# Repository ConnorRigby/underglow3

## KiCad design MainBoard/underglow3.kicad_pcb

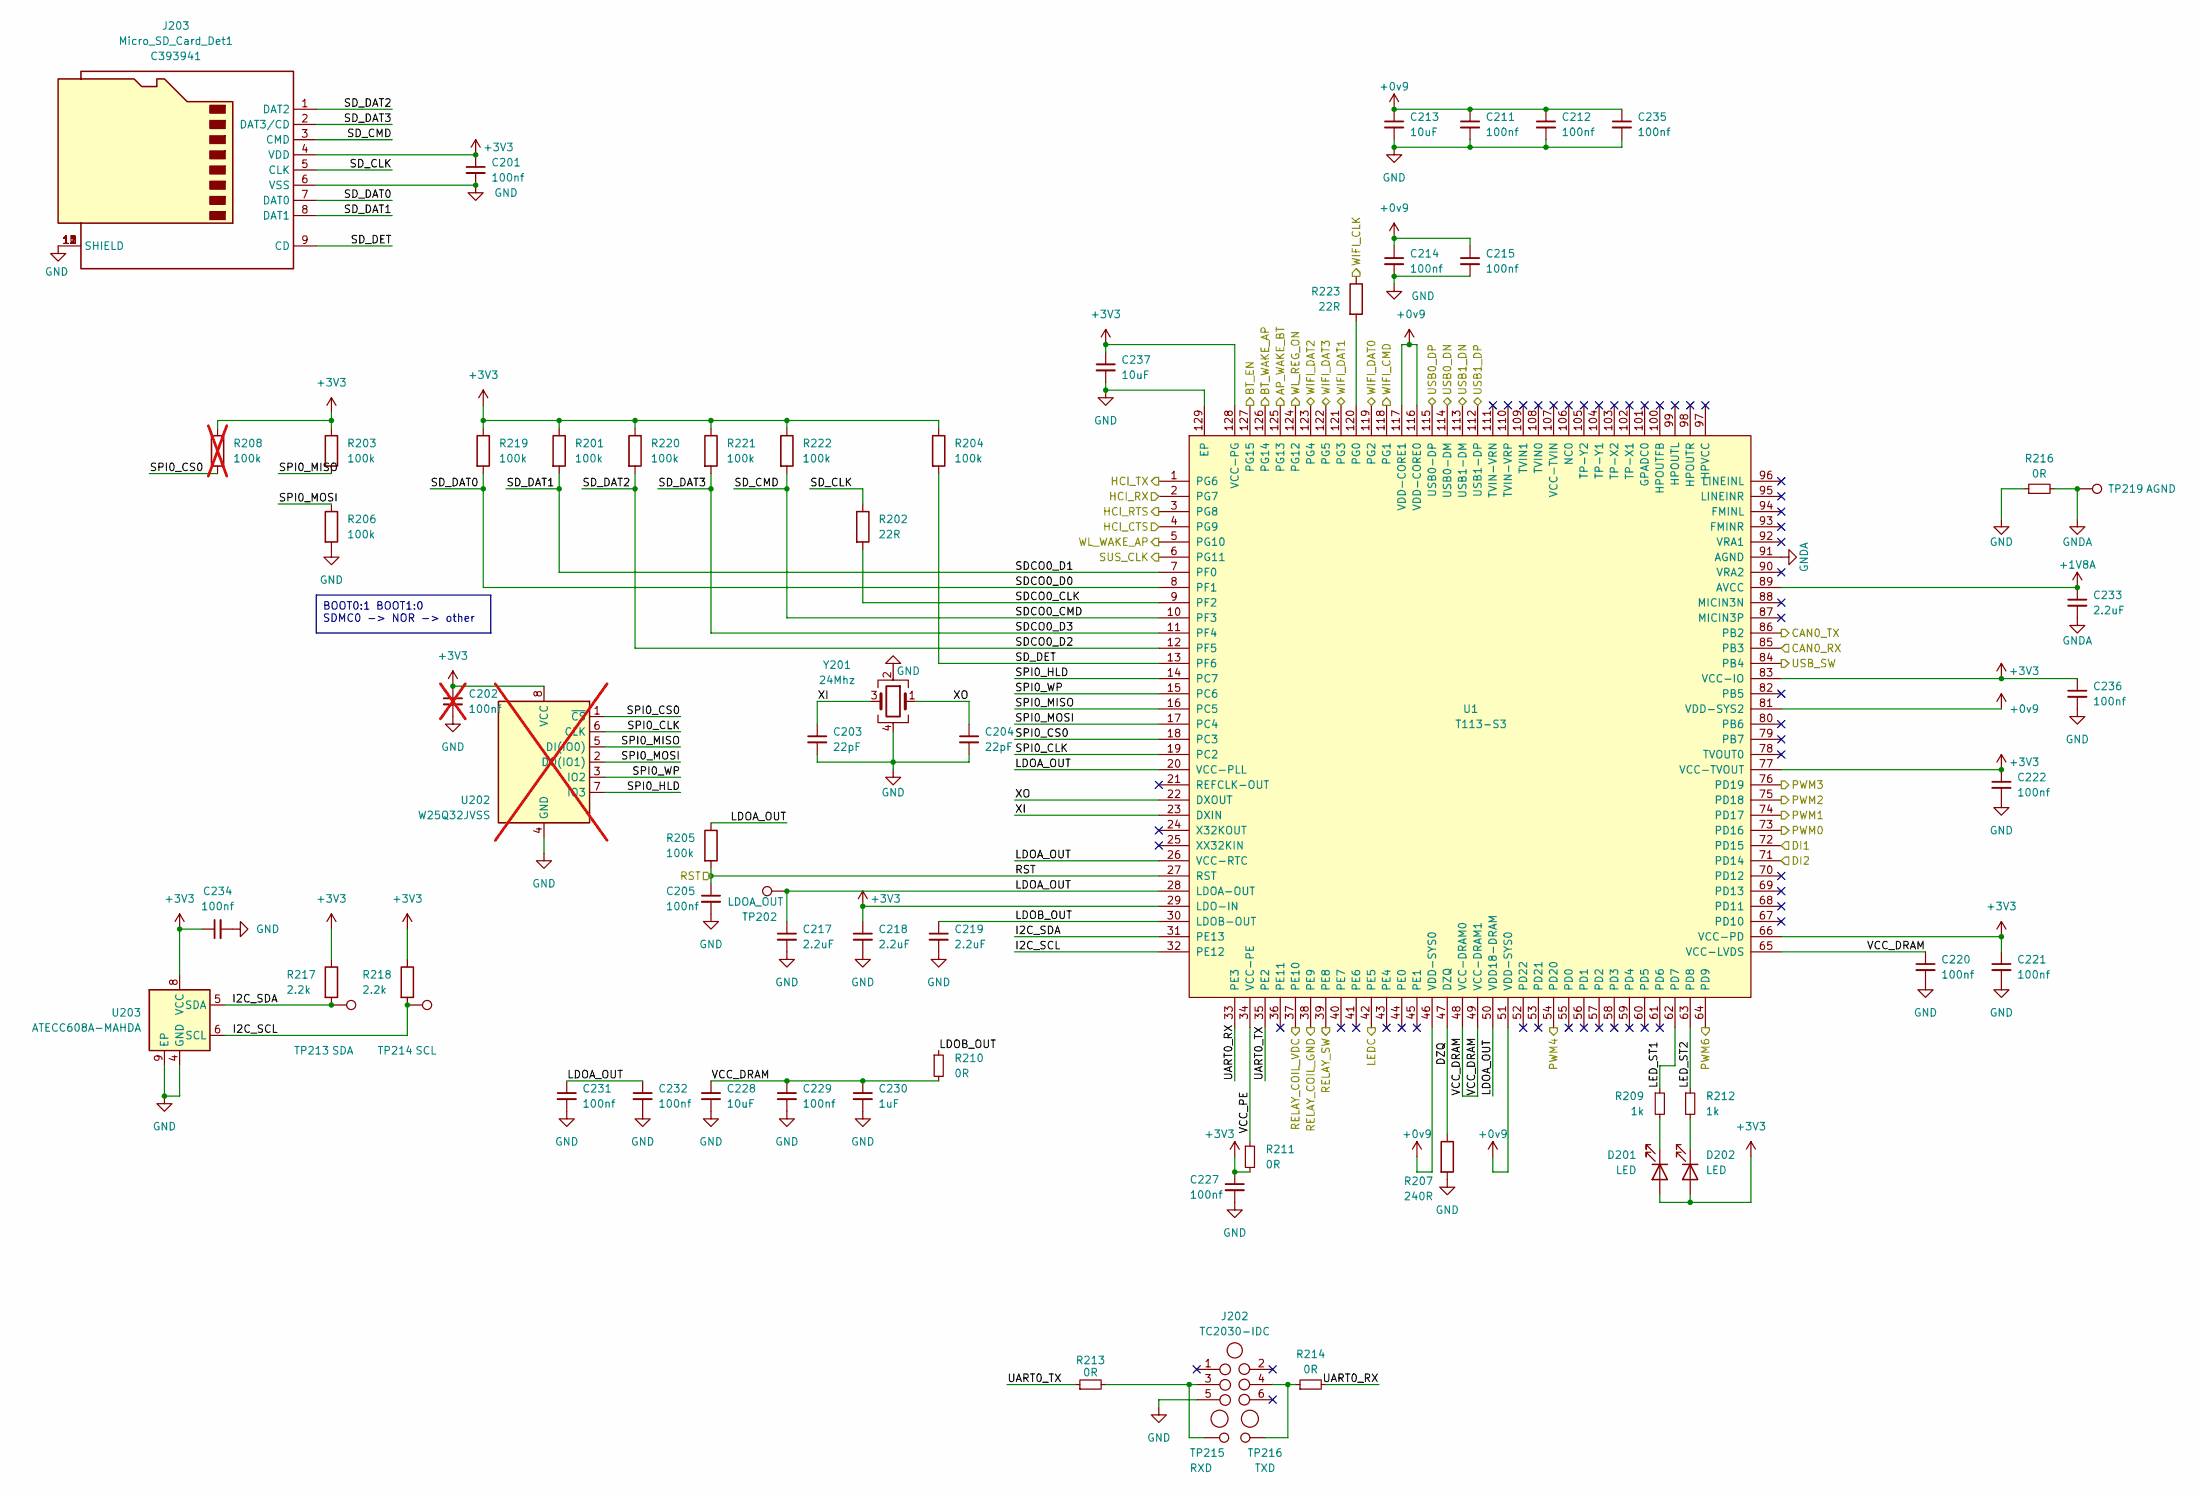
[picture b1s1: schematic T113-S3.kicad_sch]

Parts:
C201, C205, C211, C212, C214, C215, C220, C221, C222, C227, C229, C231, C232, C234, C235, C236: 100nf; C_0402_1005Metric; MPN CL05B104KB54PNC; LCSC C307331
C202: 100nf; C_0402_1005Metric; MPN CL05B104KB54PNC; LCSC C307331; not fitted
C203, C204: 22pF; C_0402_1005Metric; MPN 0402CG220J500NT; LCSC C1555
C213, C228, C237: 10uF; C_0603_1608Metric; MPN CL10A106MA8NRNC; LCSC C96446
C217, C218, C219, C233: 2.2uF; R_0402_1005Metric; MPN CL05A225MQ5NSNC; LCSC C12530
C230: 1uF; R_0402_1005Metric; MPN CL05A105KA5NQNC; LCSC C52923
D201, D202: LED; LED_0402_1005Metric; MPN LTST-C281KRKT; LCSC C364556
J202: TC2030-IDC; Tag-Connect_TC2030-IDC-NL_2x03_P1.27mm_Vertical; MPN TC2030-IDC
J203: Micro_SD_Card_Det1; TF-SMD_TF-PUSH; MPN TF PUSH; LCSC C393941
R201, R203, R204, R205, R206, R219, R220, R221, R222: 100k; R_0402_1005Metric; MPN 0402WGF1003TCE; LCSC C25741
R202, R223: 22R; R_0402_1005Metric; MPN 0402WGF220JTCE; LCSC C25092
R207: 240R; R_0402_1005Metric; MPN 0402WGF2400TCE; LCSC C25094
R208: 100k; R_0402_1005Metric; MPN 0402WGF1003TCE; LCSC C25741; not fitted
R209, R212: 1k; R_0402_1005Metric; MPN 0402WGF1001TCE; LCSC C11702
R210, R211, R213, R214, R216: 0R; R_0402_1005Metric; MPN 0402WGF0000TCE; LCSC C17168
R217, R218: 2.2k; R_0402_1005Metric; MPN 0402WGF2201TCE; LCSC C25879
TP202: LDOA_OUT; TestPoint_Pad_D1.0mm
TP213: SDA; TestPoint_Pad_D1.0mm
TP214: SCL; TestPoint_Pad_D1.0mm
TP215: RXD; TestPoint_Pad_D1.0mm
TP216: TXD; TestPoint_Pad_D1.0mm
TP219: AGND; TestPoint_Pad_D1.0mm
U1: T113-S3; LQFP-128_L14.0-W14.0-P0.40-LS16.0-BL-EP5.6; MPN T113-S3; LCSC C5197687
U202: W25Q32JVSS; SOIC-8_5.23x5.23mm_P1.27mm; MPN W25Q32JVSSIQ; LCSC C179173; not fitted
U203: ATECC608A-MAHDA; DFN-8-1EP_3x2mm_P0.5mm_EP1.3x1.5mm; MPN ATECC608A-MAHDA-S; LCSC C616908
Y201: 24Mhz; Crystal_SMD_3225-4Pin_3.2x2.5mm; MPN 3TJ424000XYFBC; LCSC C2149059

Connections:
+0v9: C211.1, C212.1, C213.1, C214.1, C215.1, C235.1; also elsewhere on the board
+1V8A: C233.1; also elsewhere on the board
+3V3: C201.1, C202.1, C218.1, C221.1, C222.1, C227.1, C234.1, C236.1, C237.1, D201.2 (A), D202.2 (A), J203.4 (VDD), R201.1, R203.1, R204.1, R208.1, R211.2, R217.1, R218.1, R219.1, R220.1, R221.1, R222.1, U202.8 (VCC), U203.8 (VCC); also elsewhere on the board
/Application/DZQ: R207.1; also elsewhere on the board
/Application/I2C_SCL: R218.2, TP214.1, U203.6 (SCL); also elsewhere on the board
/Application/I2C_SDA: R217.2, TP213.1, U203.5 (SDA); also elsewhere on the board
/Application/LDOA_OUT: C217.1, C231.1, C232.1, R205.1, TP202.1; also elsewhere on the board
/Application/LDOB_OUT: C219.1, R210.1; also elsewhere on the board
/Application/LED_ST1: R209.1; also elsewhere on the board
/Application/LED_ST2: R212.1; also elsewhere on the board
/Application/RST: C205.1, R205.2; also elsewhere on the board
/Application/SDCO0_CLK: R202.2; also elsewhere on the board
/Application/SDCO0_CMD: J203.3 (CMD), R222.2; also elsewhere on the board
/Application/SDCO0_D0: J203.7 (DAT0), R219.2; also elsewhere on the board
/Application/SDCO0_D1: J203.8 (DAT1), R201.2; also elsewhere on the board
/Application/SDCO0_D2: J203.1 (DAT2), R220.2; also elsewhere on the board
/Application/SDCO0_D3: J203.2 (DAT3/CD), R221.2; also elsewhere on the board
/Application/SD_CLK: J203.5 (CLK), R202.1
/Application/SD_DET: J203.9 (CD), R204.2; also elsewhere on the board
/Application/SPI0_CLK: U202.6 (CLK); also elsewhere on the board
/Application/SPI0_CS0: R208.2, U202.1 (~CS); also elsewhere on the board
/Application/SPI0_HLD: U202.7 (IO3); also elsewhere on the board
/Application/SPI0_MISO: R203.2, U202.5 (DI(IO0)); also elsewhere on the board
/Application/SPI0_MOSI: R206.1, U202.2 (DO(IO1)); also elsewhere on the board
/Application/SPI0_WP: U202.3 (IO2); also elsewhere on the board
/Application/UART0_RX: R214.2; also elsewhere on the board
/Application/UART0_TX: R213.1; also elsewhere on the board
/Application/VCC_DRAM: C220.1, C228.1, C229.1, C230.1, R210.2; also elsewhere on the board
/Application/VCC_PE: R211.1; also elsewhere on the board
/Application/WIFI_CLK: R223.1; also elsewhere on the board
/Application/XI: C203.1, Y201.3; also elsewhere on the board
/Application/XO: C204.1, Y201.1; also elsewhere on the board
GND: C201.2, C202.2, C203.2, C204.2, C205.2, C211.2, C212.2, C213.2, C214.2, C215.2, C217.2, C218.2, C219.2, C220.2, C221.2, C222.2, C227.2, C228.2, C229.2, C230.2, C231.2, C232.2, C234.2, C235.2, C236.2, C237.2, J202.5, J203.6 (VSS), J203.10 (SHIELD), J203.11 (SHIELD), J203.12 (SHIELD), J203.13 (SHIELD), R206.2, R207.2, R216.1, U202.4 (GND), U203.4 (GND), U203.9 (EP), Y201.2, Y201.4; also elsewhere on the board
GNDA: C233.2, R216.2, TP219.1; also elsewhere on the board
unnamed: D201.1 (K), R209.2
unnamed: D202.1 (K), R212.2
unnamed: J202.3, R213.2, TP215.1
unnamed: J202.4, R214.1, TP216.1
unnamed 130: R223.2; also elsewhere on the board

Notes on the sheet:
BOOT0:1 BOOT1:0 SDMC0 -> NOR -> other

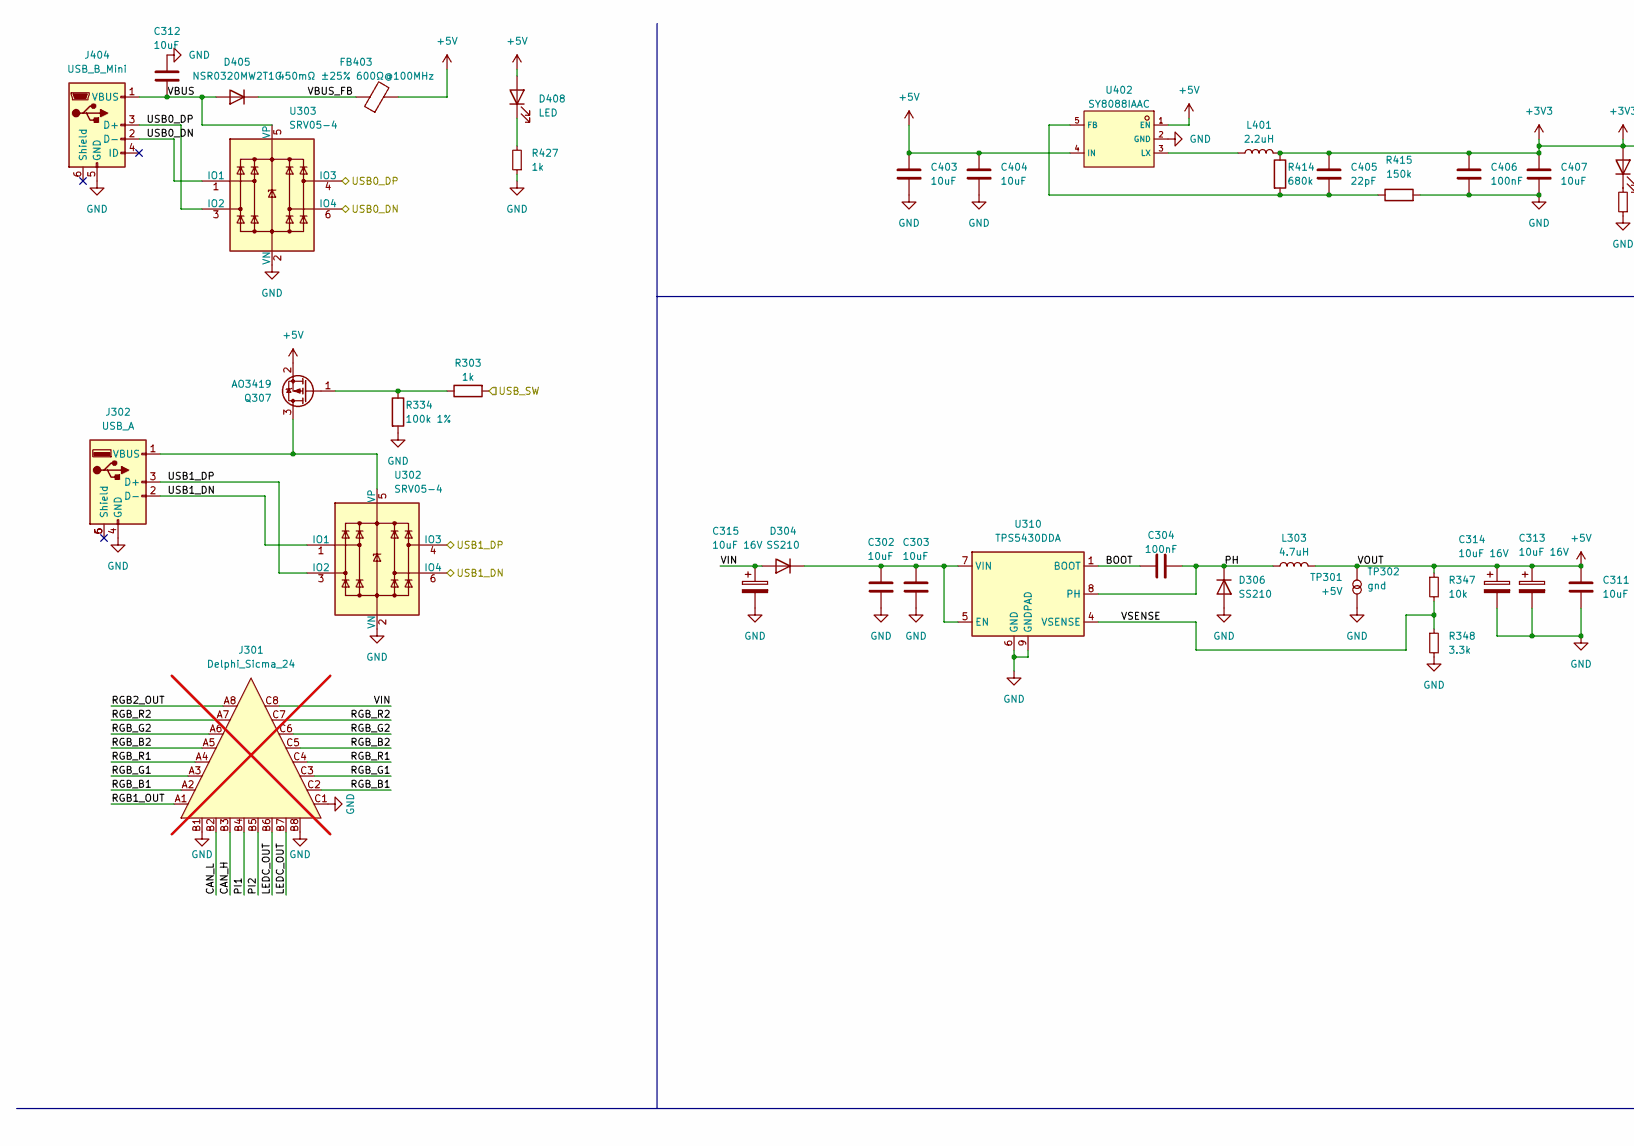
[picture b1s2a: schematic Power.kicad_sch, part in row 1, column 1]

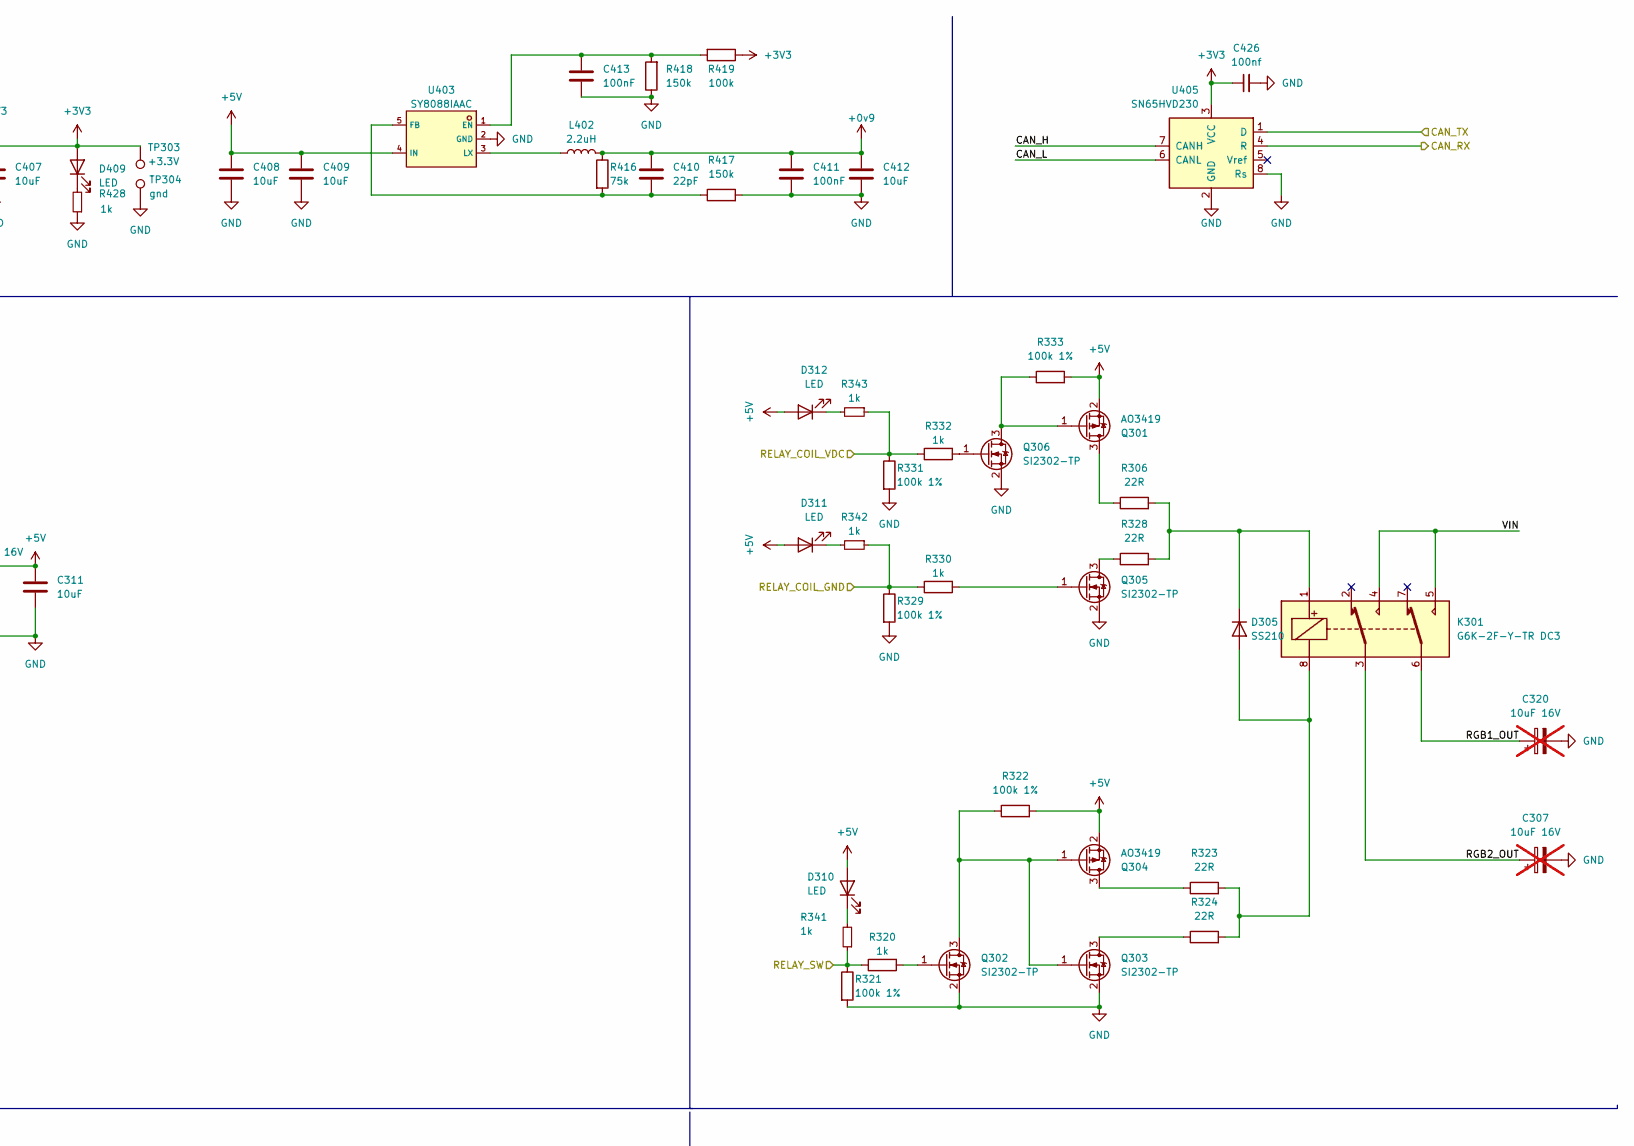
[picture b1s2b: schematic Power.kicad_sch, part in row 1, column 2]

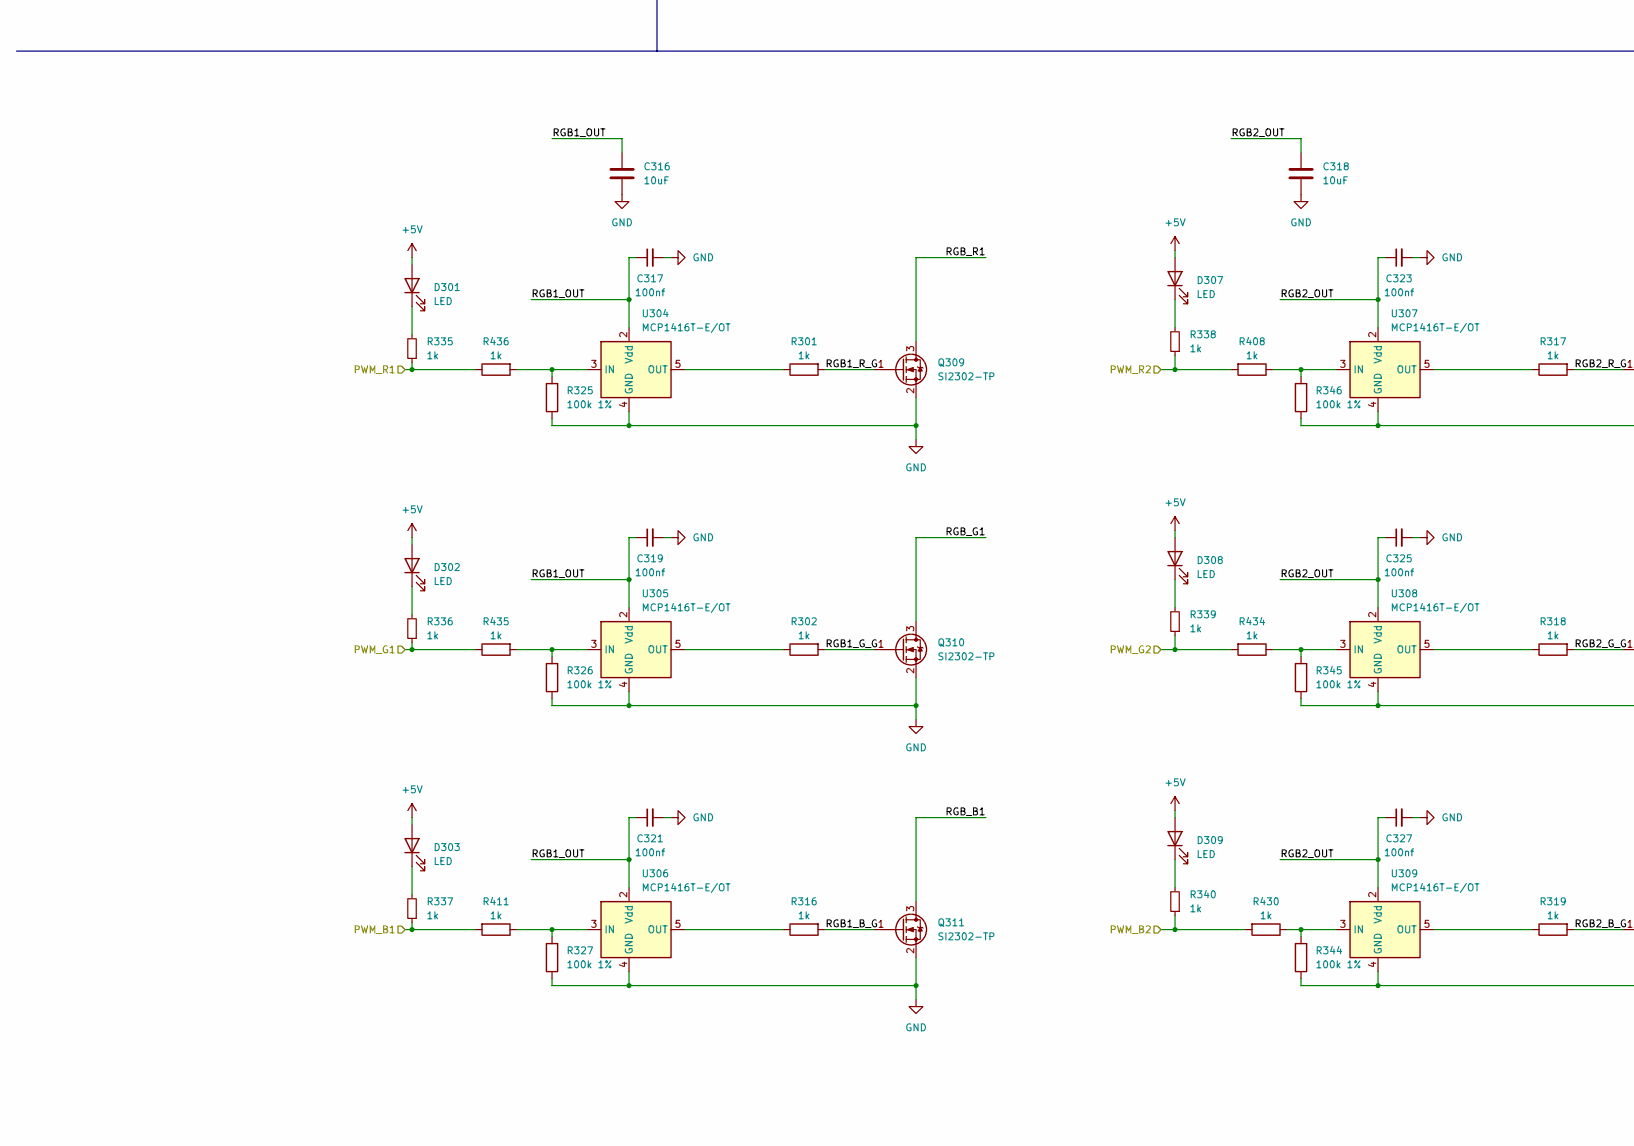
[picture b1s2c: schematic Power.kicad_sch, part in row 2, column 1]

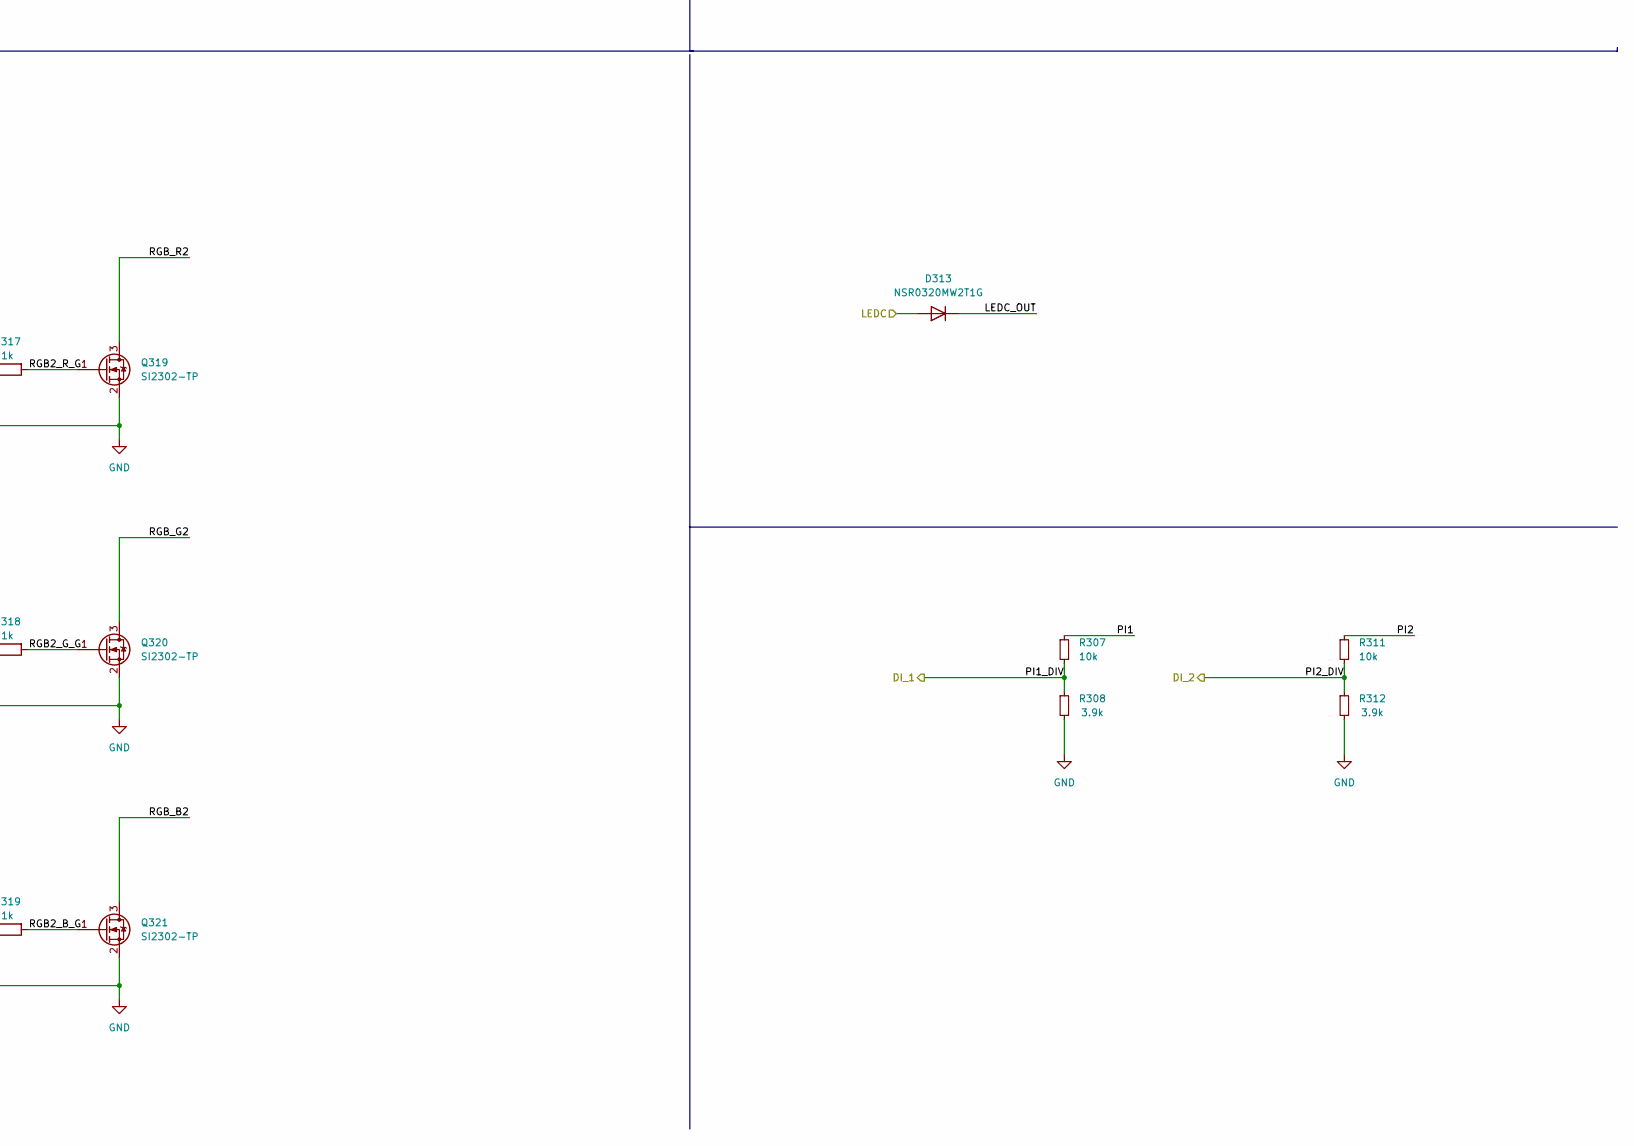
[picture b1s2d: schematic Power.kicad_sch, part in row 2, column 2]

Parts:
C302, C303, C311, C312: 10uF; C_0603_1608Metric; MPN CL10A106MA8NRNC; LCSC C96446
C304, C406, C411, C413: 100nF; C_0402_1005Metric; MPN CL05B104KB54PNC; LCSC C307331
C307, C320: 10uF 16V; CP_EIA-3216-18_Kemet-A; MPN TAJA106K016RNJ; LCSC C7171; not fitted
C313, C314, C315: 10uF 16V; CP_EIA-3216-18_Kemet-A; MPN TAJA106K016RNJ; LCSC C7171
C316, C318, C403, C404, C407, C408, C409, C412: 10uF; C_0603_1608Metric; MPN CL10A106KP8NNNC; LCSC C19702
C317, C319, C321, C323, C325, C327, C426: 100nf; C_0402_1005Metric; MPN CL05B104KB54PNC; LCSC C307331
C405, C410: 22pF; C_0402_1005Metric; MPN 0402CG220J500NT; LCSC C1555
D301, D302, D303, D307, D308, D309, D310, D311, D312, D408, D409: LED; LED_0402_1005Metric; MPN LTST-C281KRKT; LCSC C364556
D304, D305, D306: SS210; D_SMA; MPN SS210; LCSC C14996
D313, D405: NSR0320MW2T1G; D_SOD-323; MPN 1N5819WS; LCSC C191023
FB403: 450mΩ ±25% 600Ω@100MHz; L_0603_1608Metric; MPN GZ1608D601TF; LCSC C1002
J301: Delphi_Sicma_24; Delphi_Sicma_24_Black; MPN Delphi_Sicma_24; not fitted
J302: USB_A; USB-A-SMD_USB-234-BCW; MPN USB-234-BCW; LCSC C720528
J404: USB_B_Mini; USB_Mini-B_Lumberg_2486_01_Horizontal; MPN UX-144S-ACP5; LCSC C720611
K301: G6K-2F-Y-TR DC3; Relay_DPDT_Omron_G6K-2F-Y; MPN G6K-2F-Y-TR DC3; LCSC C2153097
L303: 4.7uH; IND-SMD_L7.3-W7.3; MPN CD105-4R7M 4.7UH; LCSC C2826710
L401, L402: 2.2uH; IND-SMD_L2.0-W1.6_VLS201610CX-150M; MPN WPN201610H2R2MT; LCSC C97005
Q301, Q304, Q307: AO3419; SOT-23W; MPN AO3419; LCSC C88053
Q302, Q303, Q305, Q306: SI2302-TP; SOT-23; MPN SI2302-TP; LCSC C77977
Q309, Q310, Q311, Q319, Q320, Q321: SI2302-TP; SOT-23-3; MPN AO3400A; LCSC C20917
R301, R302, R303, R316, R317, R318, R319, R320, R330, R332, R335, R336, R337, R338, R339, R340, R341, R342, R343, R408, R411, R427, R428, R430, R434, R435, R436: 1k; R_0402_1005Metric; MPN 0402WGF1001TCE; LCSC C11702
R306, R323, R324, R328: 22R; R_0402_1005Metric; MPN 0402WGF220JTCE; LCSC C25092
R307, R311, R347: 10k; R_0402_1005Metric; MPN 0402WGF1002TCE; LCSC C25744
R308, R312: 3.9k; R_0402_1005Metric; MPN 0402WGF3901TCE; LCSC C51721
R321, R322, R325, R326, R327, R329, R331, R333, R334, R344, R345, R346: 100k 1%; R_0402_1005Metric; MPN 0402WGF1003TCE; LCSC C25741
R348: 3.3k; R_0402_1005Metric; MPN 0402WGF3301TCE; LCSC C25890
R414: 680k; R_0402_1005Metric; MPN 0402WGF6803TCE; LCSC C4131
R415, R417, R418: 150k; R_0402_1005Metric; MPN 0402WGF1503TCE; LCSC C25755
R416: 75k; R_0402_1005Metric; MPN 0402WGF7502TCE; LCSC C25798
R419: 100k; R_0402_1005Metric; MPN 0402WGF1003TCE; LCSC C25741
TP301: +5V; TestPoint_Pad_D1.0mm
TP302, TP304: gnd; TestPoint_Pad_D1.0mm
TP303: +3.3V; TestPoint_Pad_D1.0mm
U302, U303: SRV05-4; SOT-23-6; MPN SRV05-4; LCSC C7420376
U304, U305, U306, U307, U308, U309: MCP1416T-E/OT; SOT-23-5; MPN MCP1416T-E/OT; LCSC C83775
U310: TPS5430DDA; TI_SO-PowerPAD-8_ThermalVias; MPN TPS5430DDA; LCSC C9864
U402, U403: SY8088IAAC; SOT-23-5; MPN SY8088IAAC; LCSC C479072
U405: SN65HVD230; SOIC-8_3.9x4.9mm_P1.27mm; MPN SN65HVD230DR; LCSC C12084

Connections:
+0v9: C410.1, C411.1, C412.1, L402.2, R416.1; also elsewhere on the board
+3V3: C405.1, C406.1, C407.1, C426.1, D409.2 (A), L401.2, R414.1, R419.1, TP303.1, U405.3 (VCC); also elsewhere on the board
+5V: C311.1, C313.1, C314.1, C403.1, C404.1, C408.1, C409.1, D301.2 (A), D302.2 (A), D303.2 (A), D307.2 (A), D308.2 (A), D309.2 (A), D310.2 (A), D311.2 (A), D312.2 (A), D408.2 (A), FB403.2, L303.2, Q301.2 (S), Q304.2 (S), Q307.2 (S), R322.2, R333.2, R347.1, TP301.1, U402.1 (EN), U402.4 (IN), U403.4 (IN)
/Application/CAN0_RX: U405.4 (R); also elsewhere on the board
/Application/CAN0_TX: U405.1 (D); also elsewhere on the board
/Application/LEDC: D313.2 (A); also elsewhere on the board
/Application/PWM0: R340.1, R430.2; also elsewhere on the board
/Application/PWM1: R335.1, R436.1; also elsewhere on the board
/Application/PWM2: R336.1, R435.1; also elsewhere on the board
/Application/PWM3: R337.1, R411.2; also elsewhere on the board
/Application/PWM4: R338.1, R408.2; also elsewhere on the board
/Application/PWM6: R339.1, R434.2; also elsewhere on the board
/Application/RELAY_COIL_GND: R329.1, R330.1, R342.1; also elsewhere on the board
/Application/RELAY_COIL_VDC: R331.1, R332.1, R343.1; also elsewhere on the board
/Application/RELAY_SW: R320.1, R321.1, R341.1; also elsewhere on the board
/Application/USB_SW: R303.2; also elsewhere on the board
/Power/BOOT: C304.1, U310.1 (BOOT)
/Power/CAN_H: J301.B3, U405.7 (CANH)
/Power/CAN_L: J301.B2, U405.6 (CANL)
/Power/LEDC_OUT: D313.1 (K), J301.B6, J301.B7
/Power/PH: C304.2, D306.1 (K), L303.1, U310.8 (PH)
/Power/PI1: J301.B4, R307.1
/Power/PI1_DIV: R307.2, R308.1; also elsewhere on the board
/Power/PI2: J301.B5, R311.1
/Power/PI2_DIV: R311.2, R312.1; also elsewhere on the board
/Power/RGB1_B_G: Q311.1 (G), R316.2
/Power/RGB1_G_G: Q310.1 (G), R302.2
/Power/RGB1_OUT: C316.1, C317.1, C319.1, C320.1, C321.1, J301.A1, K301.6, U304.2 (Vdd), U305.2 (Vdd), U306.2 (Vdd)
/Power/RGB1_R_G: Q309.1 (G), R301.2
/Power/RGB2_B_G: Q321.1 (G), R319.2
/Power/RGB2_G_G: Q320.1 (G), R318.2
/Power/RGB2_OUT: C307.1, C318.1, C323.1, C325.1, C327.1, J301.A8, K301.3, U307.2 (Vdd), U308.2 (Vdd), U309.2 (Vdd)
/Power/RGB2_R_G: Q319.1 (G), R317.2
/Power/RGB_B1: J301.A2, J301.C2, Q311.3 (D)
/Power/RGB_B2: J301.A5, J301.C5, Q321.3 (D)
/Power/RGB_G1: J301.A3, J301.C3, Q310.3 (D)
/Power/RGB_G2: J301.A6, J301.C6, Q320.3 (D)
/Power/RGB_R1: J301.A4, J301.C4, Q309.3 (D)
/Power/RGB_R2: J301.A7, J301.C7, Q319.3 (D)
/Power/USB0_DN: J404.2 (D-), U303.1 (IO1), U303.6 (IO4); also elsewhere on the board
/Power/USB0_DP: J404.3 (D+), U303.3 (IO2), U303.4 (IO3); also elsewhere on the board
/Power/USB1_DN: J302.2 (D-), U302.1 (IO1), U302.6 (IO4); also elsewhere on the board
/Power/USB1_DP: J302.3 (D+), U302.3 (IO2), U302.4 (IO3); also elsewhere on the board
/Power/VBUS: C312.2, D405.2 (A), J404.1 (VBUS), U303.5 (VP)
/Power/VBUS_FB: D405.1 (K), FB403.1
/Power/VIN: C315.1, D304.2 (A), J301.C8, K301.4, K301.5
/Power/VSENSE: R347.2, R348.1, U310.4 (VSENSE)
GND: C302.2, C303.2, C307.2, C311.2, C312.1, C313.2, C314.2, C315.2, C316.2, C317.2, C318.2, C319.2, C320.2, C321.2, C323.2, C325.2, C327.2, C403.2, C404.2, C406.2, C407.2, C408.2, C409.2, C411.2, C412.2, C413.2, C426.2, D306.2 (A), J301.B1, J301.B8, J301.C1, J302.4 (GND), J404.5 (GND), Q302.2 (S), Q303.2 (S), Q305.2 (S), Q306.2 (S), Q309.2 (S), Q310.2 (S), Q311.2 (S), Q319.2 (S), Q320.2 (S), Q321.2 (S), R308.2, R312.2, R321.2, R325.1, R326.1, R327.1, R329.2, R331.2, R334.2, R344.1, R345.1, R346.1, R348.2, R415.2, R417.2, R418.1, R427.1, R428.1, TP302.1, TP304.1, U302.2 (VN), U303.2 (VN), U304.4 (GND), U305.4 (GND), U306.4 (GND), U307.4 (GND), U308.4 (GND), U309.4 (GND), U310.6 (GND), U310.9 (GNDPAD), U402.2 (GND), U403.2 (GND), U405.2 (GND), U405.8 (Rs); also elsewhere on the board
unnamed: D301.1 (K), R335.2
unnamed: D302.1 (K), R336.2
unnamed: D303.1 (K), R337.2
unnamed: C302.1, C303.1, D304.1 (K), U310.5 (EN), U310.7 (VIN)
unnamed: D305.2 (A), K301.8, R323.2, R324.2
unnamed: D305.1 (K), K301.1, R306.2, R328.2
unnamed: D307.1 (K), R338.2
unnamed: D308.1 (K), R339.2
unnamed: D309.1 (K), R340.2
unnamed: D310.1 (K), R341.2
unnamed: D311.1 (K), R342.2
unnamed: D312.1 (K), R343.2
unnamed: D408.1 (K), R427.2
unnamed: D409.1 (K), R428.2
unnamed: J302.1 (VBUS), Q307.3 (D), U302.5 (VP)
unnamed: Q301.3 (D), R306.1
unnamed: Q301.1 (G), Q306.3 (D), R333.1
unnamed: Q302.3 (D), Q303.1 (G), Q304.1 (G), R322.1
unnamed: Q302.1 (G), R320.2
unnamed: Q303.3 (D), R324.1
unnamed: Q304.3 (D), R323.1
unnamed: Q305.3 (D), R328.1
unnamed: Q305.1 (G), R330.2
unnamed: Q306.1 (G), R332.2
unnamed: Q307.1 (G), R303.1, R334.1
unnamed: R325.2, R436.2, U304.3 (IN)
unnamed: R301.1, U304.5 (OUT)
unnamed: R326.2, R435.2, U305.3 (IN)
unnamed: R302.1, U305.5 (OUT)
unnamed: R327.2, R411.1, U306.3 (IN)
unnamed: R316.1, U306.5 (OUT)
unnamed: R346.2, R408.1, U307.3 (IN)
unnamed: R317.1, U307.5 (OUT)
unnamed: R345.2, R434.1, U308.3 (IN)
unnamed: R318.1, U308.5 (OUT)
unnamed: R344.2, R430.1, U309.3 (IN)
unnamed: R319.1, U309.5 (OUT)
unnamed: C405.2, R414.2, R415.1, U402.5 (FB)
unnamed: L401.1, U402.3 (LX)
unnamed: C413.1, R418.2, R419.2, U403.1 (EN)
unnamed: C410.2, R416.2, R417.1, U403.5 (FB)
unnamed: L402.1, U403.3 (LX)

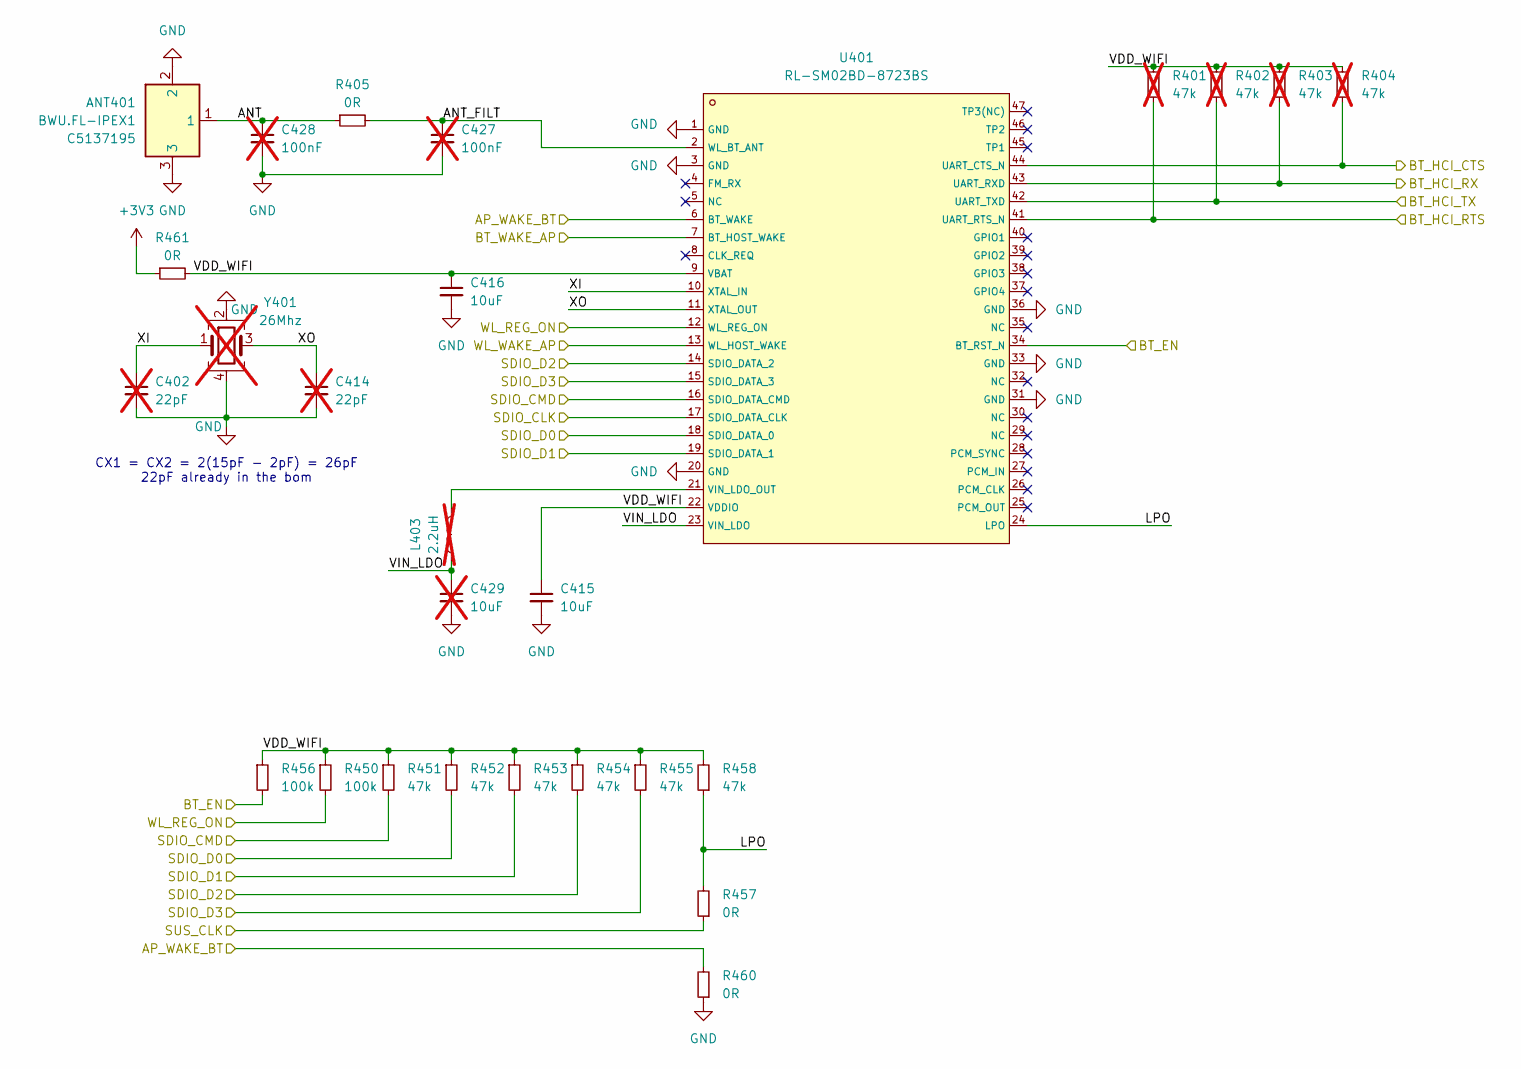
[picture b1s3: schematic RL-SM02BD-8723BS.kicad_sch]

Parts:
ANT401: BWU.FL-IPEX1; IPEX-SMD_BWIPX-1-001E; MPN BWU.FL-IPEX1; LCSC C5137195
C402, C414: 22pF; C_0402_1005Metric; MPN 0402CG220J500NT; LCSC C1555; not fitted
C415, C416: 10uF; C_0603_1608Metric; MPN CL10A106MA8NRNC; LCSC C96446
C427, C428: 100nF; R_0402_1005Metric; MPN CL05B104KB54PNC; LCSC C307331; not fitted
C429: 10uF; C_0603_1608Metric; MPN CL10A106MA8NRNC; LCSC C96446; not fitted
L403: 2.2uH; L_0603_1608Metric; MPN CPY160808T-2R2M-NP; LCSC C365953; not fitted
R401, R402, R403, R404: 47k; R_0402_1005Metric; MPN 0402WGF4702TCE; LCSC C25792; not fitted
R405, R457, R460, R461: 0R; R_0402_1005Metric; MPN 0402WGF0000TCE; LCSC C17168
R450, R456: 100k; R_0402_1005Metric; MPN 0402WGF1003TCE; LCSC C25741
R451, R452, R453, R454, R455, R458: 47k; R_0402_1005Metric; MPN 0402WGF4702TCE; LCSC C25792
U401: RL-SM02BD-8723BS; QFN-44_L12.0-W12.0-P0.90-TL_AP6212; MPN RL-SM02BD-8723BS; LCSC C9900101851
Y401: 26Mhz; Crystal_SMD_3225-4Pin_3.2x2.5mm; MPN TAXM26M4RHBCCT2T; LCSC C516065; not fitted

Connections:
+3V3: R461.1; also elsewhere on the board
/Application/AP_WAKE_BT: R460.2, U401.6 (BT_WAKE); also elsewhere on the board
/Application/BT_EN: R456.2, U401.34 (BT_RST_N); also elsewhere on the board
/Application/BT_WAKE_AP: U401.7 (BT_HOST_WAKE); also elsewhere on the board
/Application/HCI_CTS: R401.2, U401.41 (UART_RTS_N); also elsewhere on the board
/Application/HCI_RTS: R404.1, U401.44 (UART_CTS_N); also elsewhere on the board
/Application/HCI_RX: R402.2, U401.42 (UART_TXD); also elsewhere on the board
/Application/HCI_TX: R403.2, U401.43 (UART_RXD); also elsewhere on the board
/Application/SUS_CLK: R457.1; also elsewhere on the board
/Application/WIFI_CLK: U401.17 (SDIO_DATA_CLK); also elsewhere on the board
/Application/WIFI_CMD: R451.2, U401.16 (SDIO_DATA_CMD); also elsewhere on the board
/Application/WIFI_DAT0: R452.2, U401.18 (SDIO_DATA_0); also elsewhere on the board
/Application/WIFI_DAT1: R453.2, U401.19 (SDIO_DATA_1); also elsewhere on the board
/Application/WIFI_DAT2: R454.2, U401.14 (SDIO_DATA_2); also elsewhere on the board
/Application/WIFI_DAT3: R455.2, U401.15 (SDIO_DATA_3); also elsewhere on the board
/Application/WL_REG_ON: R450.2, U401.12 (WL_REG_ON); also elsewhere on the board
/Application/WL_WAKE_AP: U401.13 (WL_HOST_WAKE); also elsewhere on the board
/RL-SM02BD-8723BS/ANT: ANT401.1, C428.1, R405.1
/RL-SM02BD-8723BS/ANT_FILT: C427.1, R405.2, U401.2 (WL_BT_ANT)
/RL-SM02BD-8723BS/LPO: R457.2, R458.1, U401.24 (LPO)
/RL-SM02BD-8723BS/VDD_WIFI: C415.1, C416.1, R401.1, R402.1, R403.1, R404.2, R450.1, R451.1, R452.1, R453.1, R454.1, R455.1, R456.1, R458.2, R461.2, U401.9 (VBAT), U401.22 (VDDIO)
/RL-SM02BD-8723BS/VIN_LDO: C429.1, L403.1, U401.23 (VIN_LDO)
/RL-SM02BD-8723BS/XI: C402.1, U401.10 (XTAL_IN), Y401.1
/RL-SM02BD-8723BS/XO: C414.1, U401.11 (XTAL_OUT), Y401.3
GND: ANT401.2, ANT401.3, C402.2, C414.2, C415.2, C416.2, C427.2, C428.2, C429.2, R460.1, U401.1 (GND), U401.3 (GND), U401.20 (GND), U401.31 (GND), U401.33 (GND), U401.36 (GND), Y401.2, Y401.4; also elsewhere on the board
unnamed: L403.2, U401.21 (VIN_LDO_OUT)

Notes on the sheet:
CX1 = CX2 = 2(15pF - 2pF) = 26pF 22pF already in the bom
